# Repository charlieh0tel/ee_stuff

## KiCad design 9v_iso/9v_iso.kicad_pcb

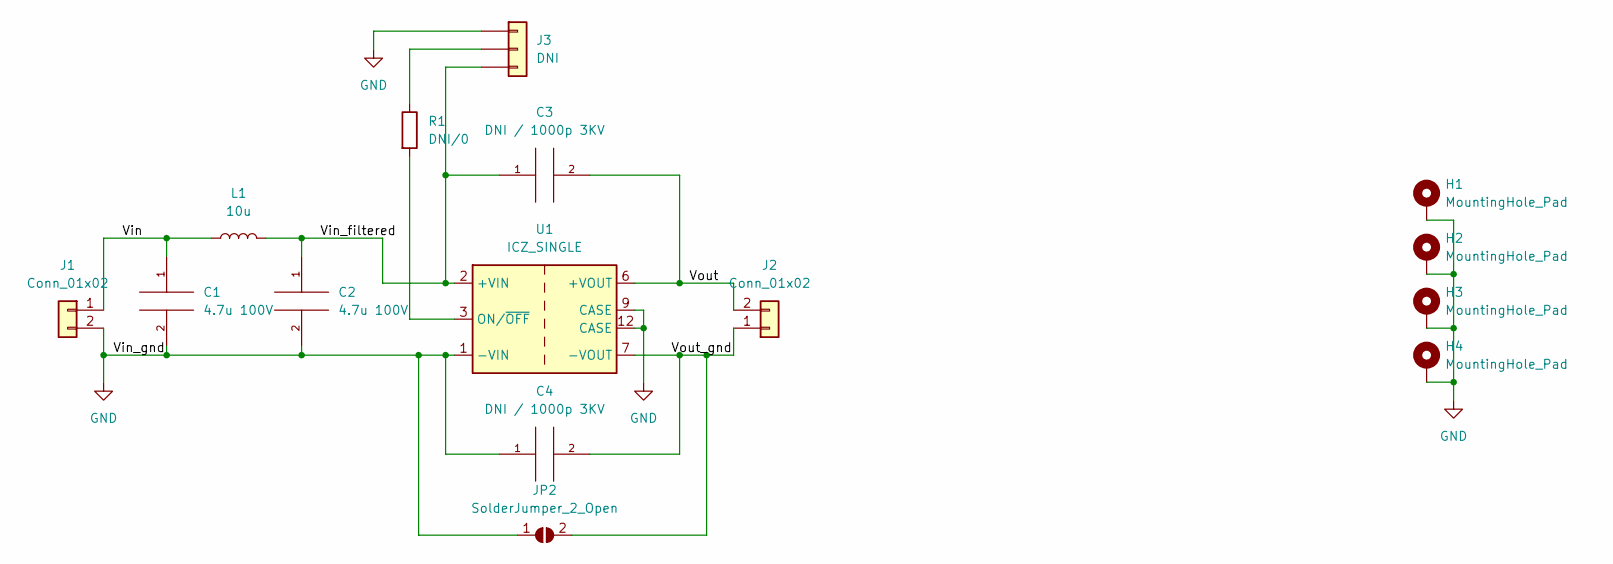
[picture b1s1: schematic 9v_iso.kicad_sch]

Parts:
C1, C2: 4.7u 100V; C_1210_3225Metric_Pad1.33x2.70mm_HandSolder
C3, C4: DNI / 1000p 3KV; C_1812_4532Metric_Pad1.57x3.40mm_HandSolder
H1, H2, H3, H4: MountingHole_Pad; MountingHole_3mm_Pad
J1, J2: Conn_01x02; TerminalBlock_bornier-2_P5.08mm
J3: DNI; PinHeader_1x03_P2.54mm_Vertical
JP2: SolderJumper_2_Open; SolderJumper-2_P1.3mm_Open_RoundedPad1.0x1.5mm
L1: 10u; L_Taiyo-Yuden_NR-24xx_HandSoldering
R1: DNI/0; R_0805_2012Metric_Pad1.20x1.40mm_HandSolder
U1: ICZ_SINGLE; CONV_ICZ0912S12

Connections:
/Vin: C1.1, J1.1, L1.1
/Vin_filtered: C2.1, C3.1, J3.3, L1.2, U1.2 (+VIN)
/Vout: C3.2, J2.2, U1.6 (+VOUT)
/Vout_gnd: C4.2, J2.1, JP2.2 (B), U1.7 (-VOUT)
GND: C1.2, C2.2, C4.1, H1.1, H2.1, H3.1, H4.1, J1.2, J3.1, JP2.1 (A), U1.1 (-VIN), U1.9 (CASE), U1.12 (CASE)
unnamed: J3.2, R1.1
unnamed: R1.2, U1.3 (ON/~OFF)

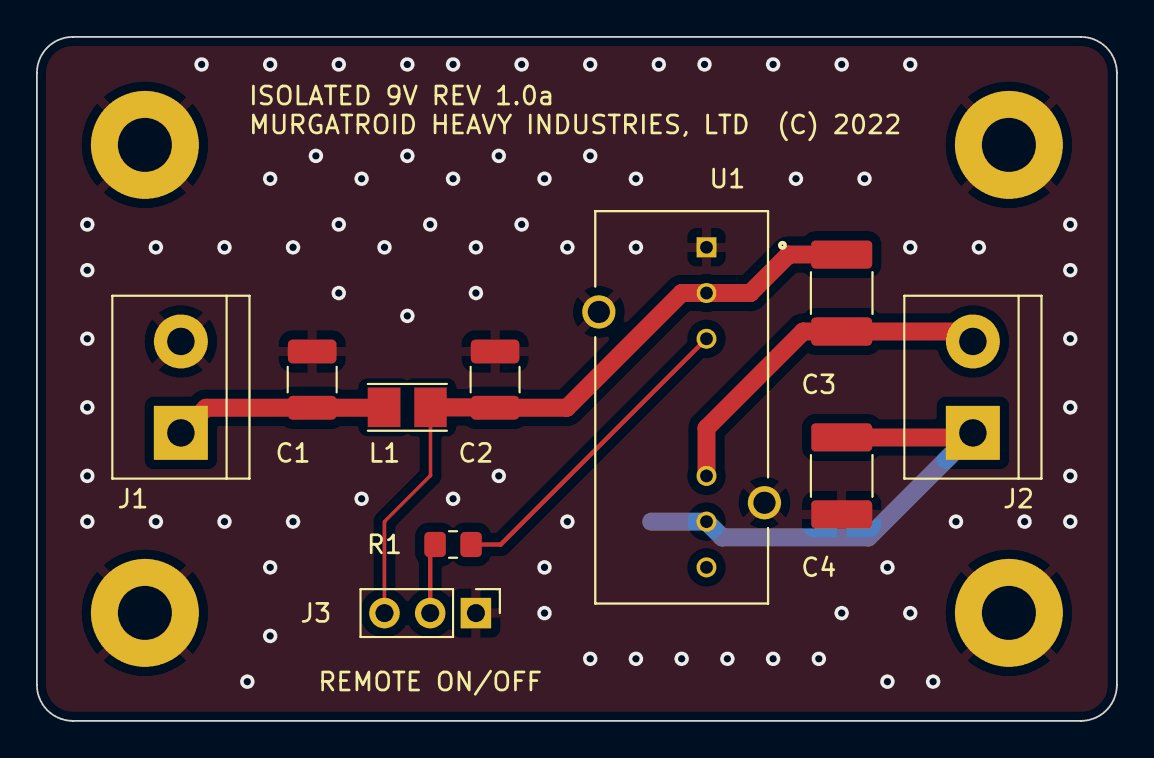
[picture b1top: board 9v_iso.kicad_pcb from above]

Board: 2 copper layers, 60.0 x 38.0 mm, 15 parts (1 on the bottom side), 7 nets.

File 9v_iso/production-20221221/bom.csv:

Designator,Footprint,Quantity,Value,LCSC Part #
"C1, C2",C_1210_3225Metric_Pad1.33x2.70mm_HandSolder,2,4.7u 100V,
"C3, C4",C_1812_4532Metric_Pad1.57x3.40mm_HandSolder,2,DNI / 1000p 3KV,
"H1, H2, H3, H4",MountingHole_3mm_Pad,4,MountingHole_Pad,
"J1, J2",TerminalBlock_bornier-2_P5.08mm,2,Conn_01x02,
J3,PinHeader_1x03_P2.54mm_Vertical,1,DNI,
JP2,SolderJumper-2_P1.3mm_Open_RoundedPad1.0x1.5mm,1,SolderJumper_2_Open,
L1,L_Taiyo-Yuden_NR-24xx_HandSoldering,1,10u,
R1,R_0805_2012Metric_Pad1.20x1.40mm_HandSolder,1,DNI/0,
U1,CONV_ICZ0912S12,1,ICZ_SINGLE,

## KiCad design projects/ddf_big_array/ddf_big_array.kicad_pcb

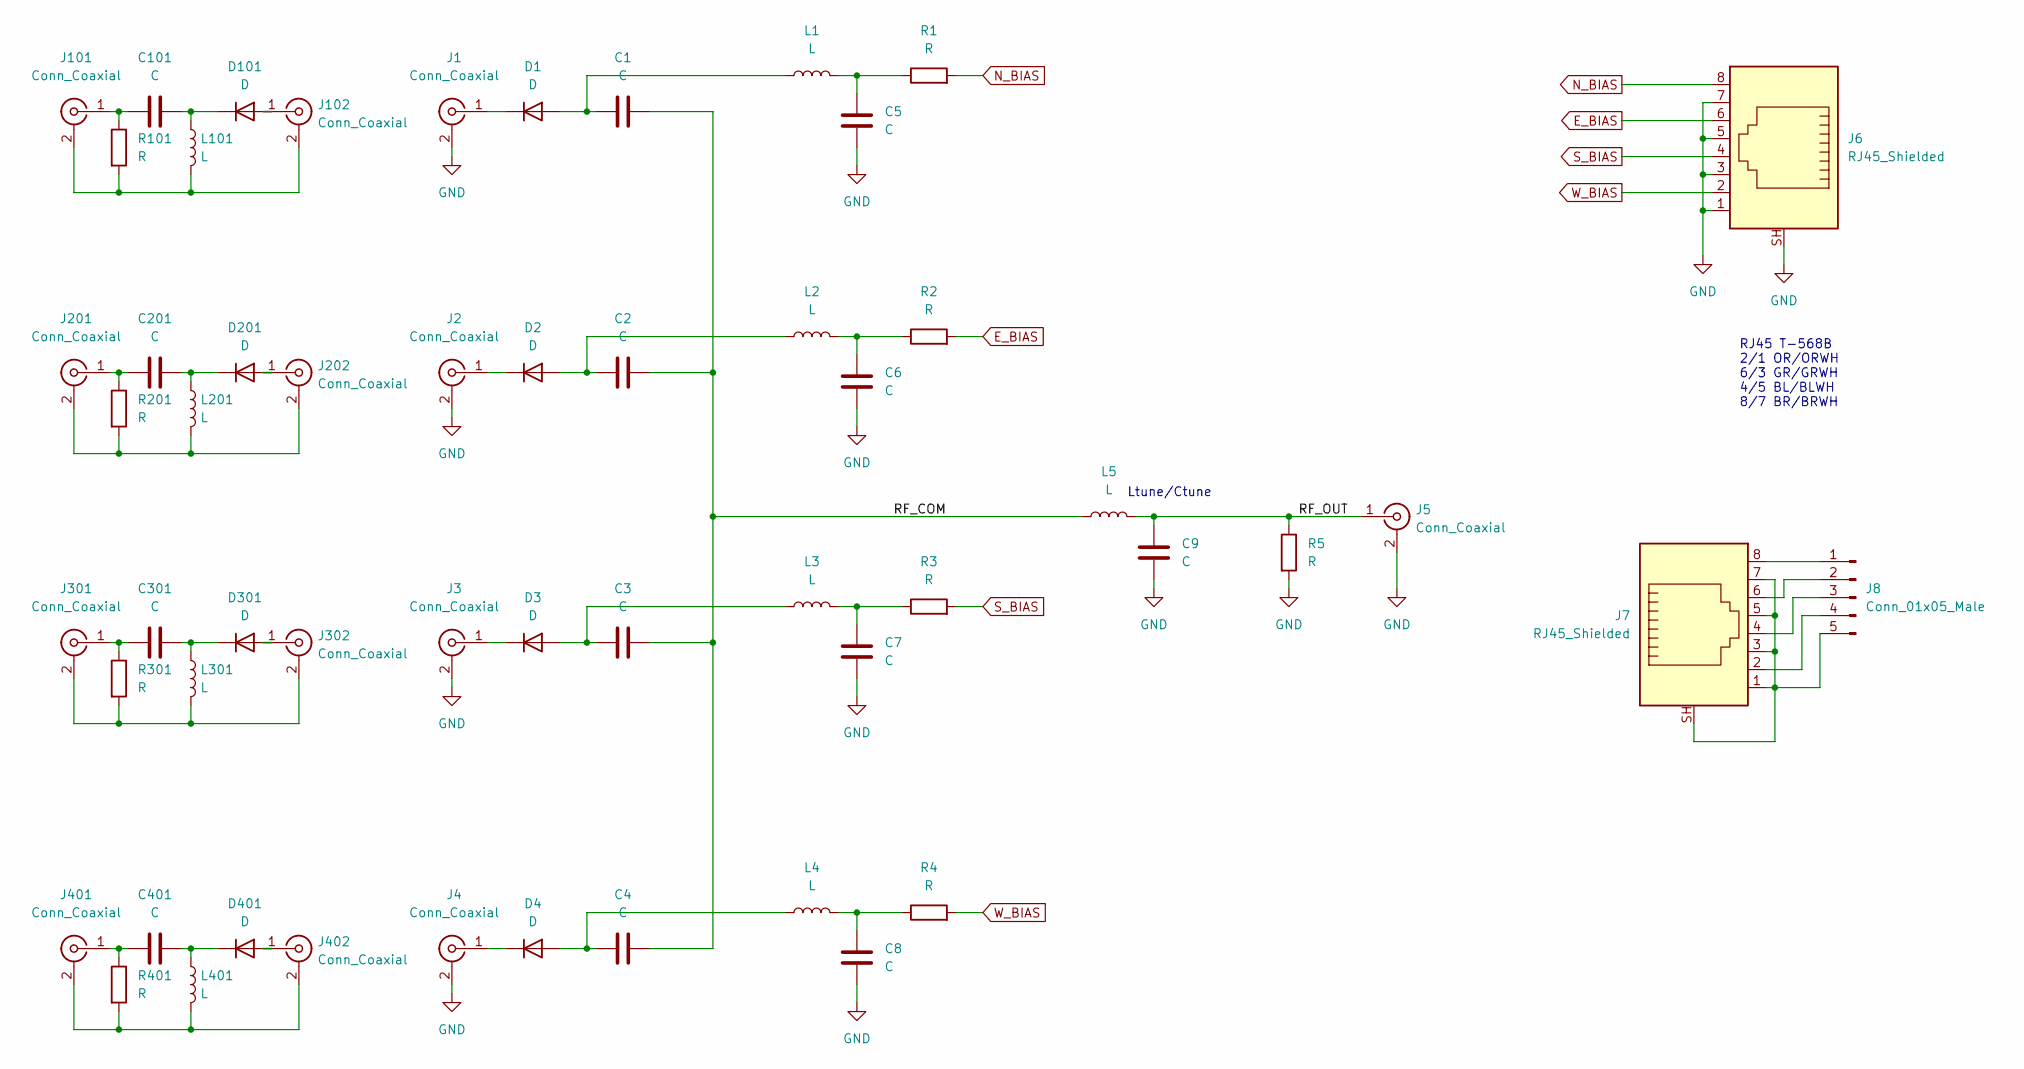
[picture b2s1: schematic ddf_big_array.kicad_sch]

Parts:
C1, C2, C3, C4, C5, C6, C7, C8, C9, C101, C201, C301, C401: C; C_0402_1005Metric_Pad0.74x0.62mm_HandSolder
D1, D2, D3, D4, D101, D201, D301, D401: D; D_SOD-523
J1, J2, J3, J4, J102, J202, J302, J402: Conn_Coaxial; SMA_Amphenol_132203-12_Horizontal
J5: Conn_Coaxial; SMA_Molex_73251-2200_Horizontal
J6, J7: RJ45_Shielded; RJ45_Wuerth_7499010001A_Horizontal
J8: Conn_01x05_Male; PinHeader_1x05_P2.54mm_Vertical
J101, J201, J301, J401: Conn_Coaxial; SMA_Amphenol_132134_Vertical
L1, L2, L3, L4, L5, L101, L201, L301, L401: L; L_0402_1005Metric_Pad0.77x0.64mm_HandSolder
R1, R2, R3, R4, R5, R101, R201, R301, R401: R; R_0402_1005Metric_Pad0.72x0.64mm_HandSolder

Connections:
/RF_COM: C1.2, C2.2, C3.2, C4.2, L5.1
/RF_OUT: C9.1, J5.1 (In), L5.2, R5.1
E_BIAS: J6.6, R2.2
GND: C5.2, C6.2, C7.2, C8.2, C9.2, J1.2 (Ext), J2.2 (Ext), J3.2 (Ext), J4.2 (Ext), J5.2 (Ext), J6.1, J6.3, J6.5, J6.7, J6.SH, R5.2
N_BIAS: J6.8, R1.2
unnamed: C1.1, D1.2 (A), L1.1
unnamed: C2.1, D2.2 (A), L2.1
unnamed: C3.1, D3.2 (A), L3.1
unnamed: C4.1, D4.2 (A), L4.1
unnamed: C5.1, L1.2, R1.1
unnamed: C6.1, L2.2, R2.1
unnamed: C7.1, L3.2, R3.1
unnamed: C8.1, L4.2, R4.1
unnamed: C101.1, J101.1 (In), R101.1
unnamed: C101.2, D101.1 (K), L101.1
unnamed: C201.1, J201.1 (In), R201.1
unnamed: C201.2, D201.1 (K), L201.1
unnamed: C301.1, J301.1 (In), R301.1
unnamed: C301.2, D301.1 (K), L301.1
unnamed: C401.1, J401.1 (In), R401.1
unnamed: C401.2, D401.1 (K), L401.1
unnamed: D1.1 (K), J1.1 (In)
unnamed: D2.1 (K), J2.1 (In)
unnamed: D3.1 (K), J3.1 (In)
unnamed: D4.1 (K), J4.1 (In)
unnamed: D101.2 (A), J102.1 (In)
unnamed: D201.2 (A), J202.1 (In)
unnamed: D301.2 (A), J302.1 (In)
unnamed: D401.2 (A), J402.1 (In)
unnamed: J7.1, J7.3, J7.5, J7.7, J7.SH, J8.5
unnamed: J7.2, J8.4
unnamed: J7.4, J8.3
unnamed: J7.6, J8.2
unnamed: J7.8, J8.1
unnamed: J101.2 (Ext), J102.2 (Ext), L101.2, R101.2
unnamed: J201.2 (Ext), J202.2 (Ext), L201.2, R201.2
unnamed: J301.2 (Ext), J302.2 (Ext), L301.2, R301.2
unnamed: J401.2 (Ext), J402.2 (Ext), L401.2, R401.2
S_BIAS: J6.4, R3.2
W_BIAS: J6.2, R4.2

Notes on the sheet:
RJ45 T-568B 2/1 OR/ORWH 6/3 GR/GRWH 4/5 BL/BLWH 8/7 BR/BRWH
Ltune/Ctune

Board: 2 copper layers, 55 parts (0 on the bottom side), 40 nets, no tracks yet.

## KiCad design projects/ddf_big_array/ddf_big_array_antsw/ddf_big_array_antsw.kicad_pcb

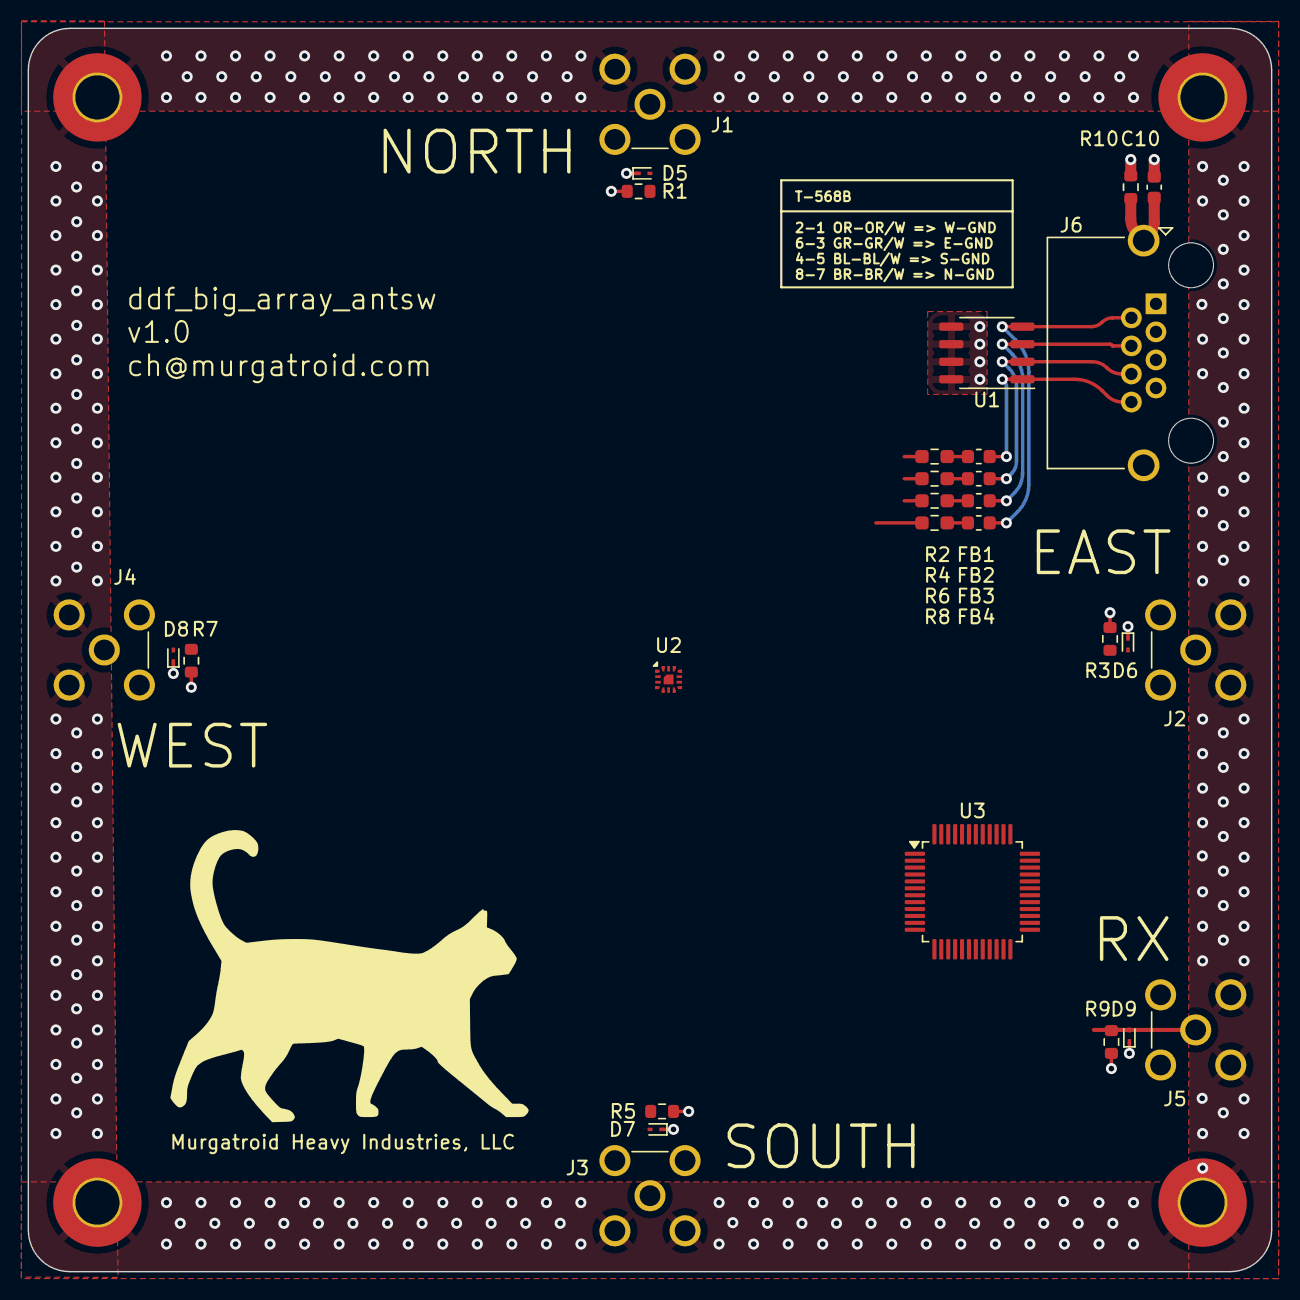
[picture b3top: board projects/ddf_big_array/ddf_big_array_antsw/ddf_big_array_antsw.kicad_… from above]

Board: 4 copper layers, 90.0 x 90.0 mm, 33 parts (0 on the bottom side), 16 nets.

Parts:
C10: 1n NP0 50V; C_0603_1608Metric
D5, D6, D7, D8, D9: ESD7951ST5G; D_SOD-923
FB1, FB2, FB3, FB4: 600R @ 100 MHz; L_0603_1608Metric
H1, H2, H3, H4: MountingHole; MountingHole_3.2mm_M3_Pad_TopBottom
J1, J2, J3, J4, J5: Conn_Coaxial; SMA_Horizontal
J6: RJ45_Shielded; RJ45_Amphenol_RJHSE5380
R1, R3, R5, R7, R9, R10: 100K; R_0603_1608Metric
R2, R4, R6, R8: 270; R_0603_1608Metric_Pad0.98x0.95mm_HandSolder
U1: SMDA05; SO-8_3.9x4.9mm_P1.27mm
U2: SKY13414-485LF; Skyworks_SKY13575_639LF
U3: STM32G0B1CBT; LQFP-48_7x7mm_P0.5mm

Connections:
+3V3: U3.4 (VBAT), U3.5 (VREF+), U3.6 (VDD/VDDA)
/E_IN: D6.2 (A2), J2.1 (In), R3.1
/N_IN: D5.2 (A2), J1.1 (In), R1.1
/RF_OUT: D9.2 (A2), J5.1 (In), R9.1
/RJ_SHIELD: C10.1, J6.SH, R10.1
/S_IN: D7.2 (A2), J3.1 (In), R5.1
/W_IN: D8.2 (A2), J4.1 (In), R7.1
E_BIAS: FB2.1, R4.2
GND: C10.2, D5.1 (A1), D6.1 (A1), D7.1 (A1), D8.1 (A1), D9.1 (A1), H1.1, H2.1, H3.1, H4.1, J1.2 (Ext), J2.2 (Ext), J3.2 (Ext), J4.2 (Ext), J5.2 (Ext), J6.1, J6.3, J6.5, J6.7, R1.2, R3.2, R5.2, R7.2, R9.2, R10.2, U1.5 (D2), U1.6 (C2), U1.7 (B2), U1.8 (A2), U2.15 (GND), U3.7 (VSS/VSSA)
N_BIAS: FB1.1, R2.2
unnamed: FB1.2, J6.8
unnamed: FB2.2, J6.6
unnamed: FB3.2, J6.4
unnamed: FB4.2, J6.2
S_BIAS: FB3.1, R6.2
W_BIAS: FB4.1, R8.2

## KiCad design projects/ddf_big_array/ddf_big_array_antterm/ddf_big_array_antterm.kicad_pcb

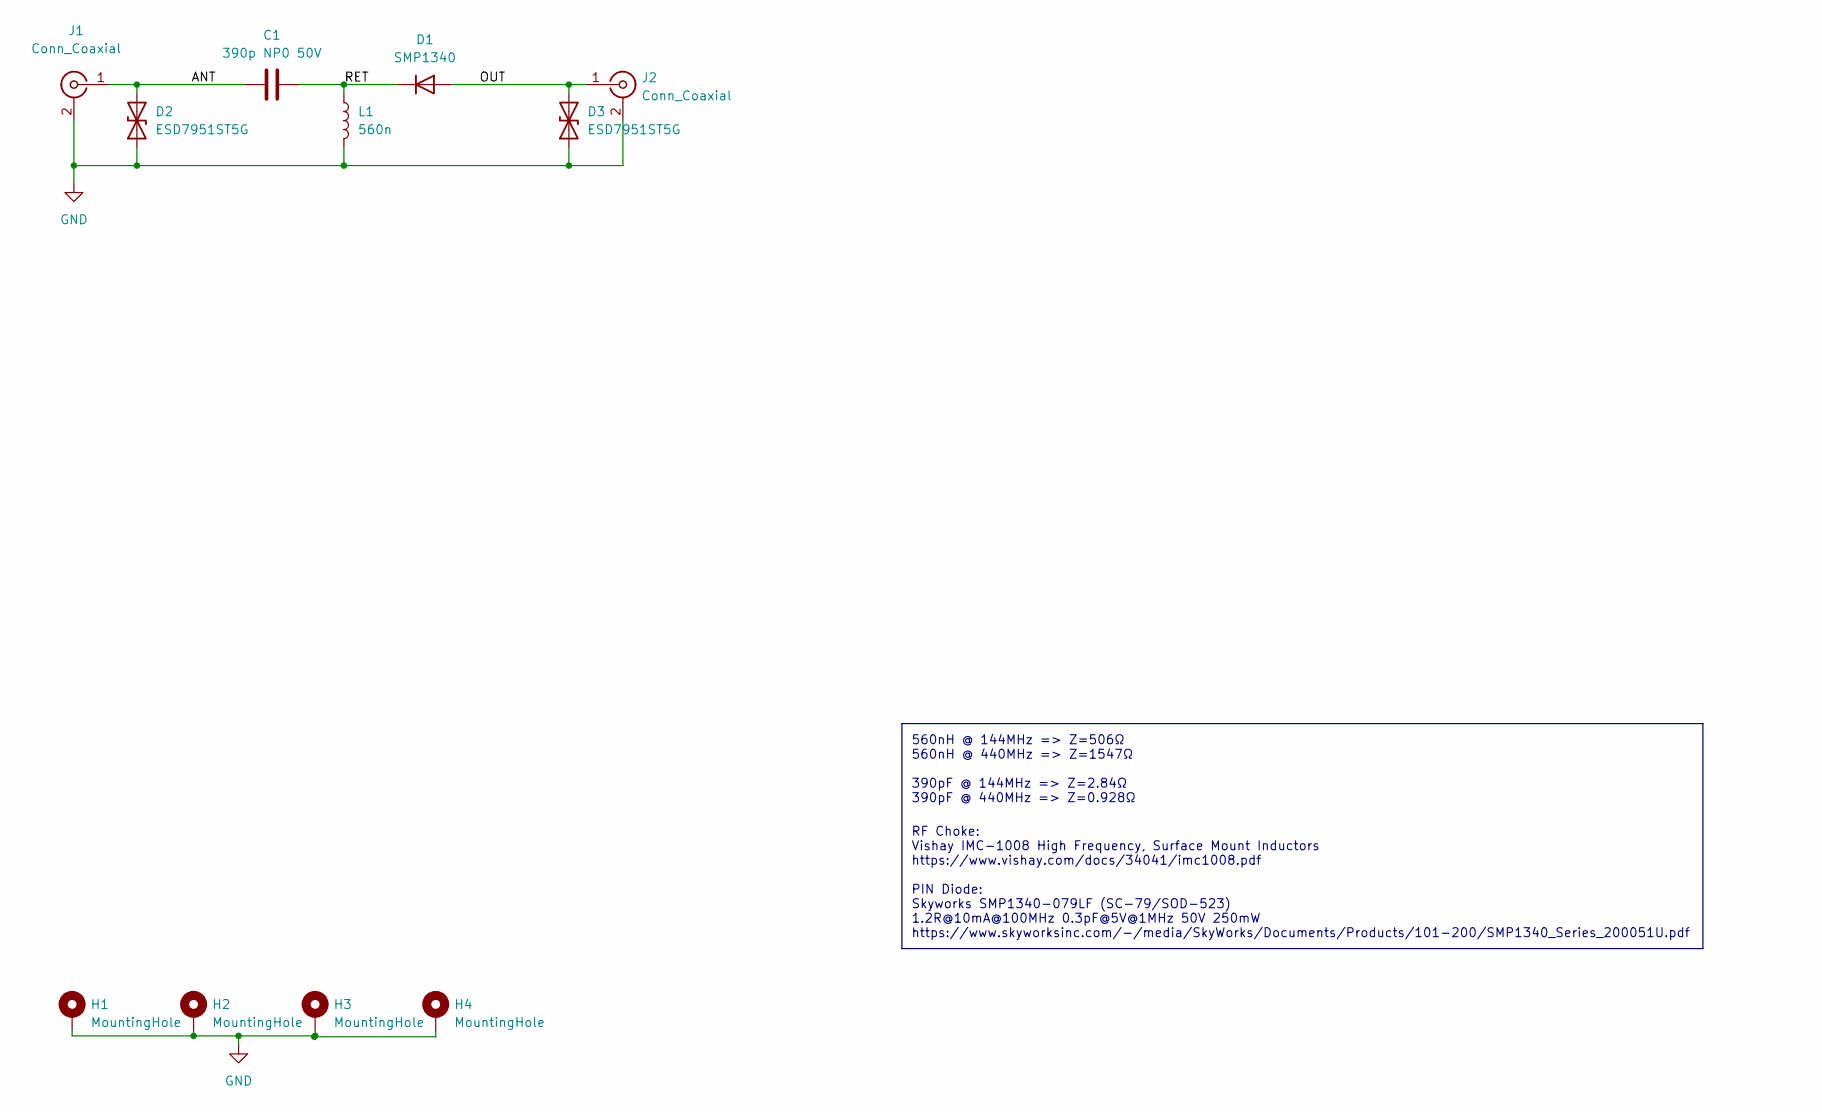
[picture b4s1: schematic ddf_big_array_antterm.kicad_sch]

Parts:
C1: 390p NP0 50V; C_0402_1005Metric; MPN GRM1555C1H391FA01D; LCSC C162100
D1: SMP1340; D_SOD-523; MPN SMP1340-079LF; LCSC C5365278
D2, D3: ESD7951ST5G; D_SOD-923; MPN ESD7951ST5G; LCSC C94375
H1, H2, H3, H4: MountingHole; MountingHole_3.2mm_M3_Pad_TopBottom
J1: Conn_Coaxial; SMA_Molex-73391-0070_Vertical; LCSC C2874833
J2: Conn_Coaxial; SMA_Horizontal; LCSC C1509208
L1: 560n; IMC1008; MPN IMC1008ERR56J; LCSC C5365279

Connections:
/ANT: C1.1, D2.2 (A2), J1.1 (In)
/OUT: D1.2 (A), D3.2 (A2), J2.1 (In)
/RET: C1.2, D1.1 (K), L1.1
GND: D2.1 (A1), D3.1 (A1), H1.1, H2.1, H3.1, H4.1, J1.2 (Ext), J2.2 (Ext), L1.2

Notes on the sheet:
RF Choke: Vishay IMC-1008 High Frequency, Surface Mount Inductors https://www.vishay.com/docs/34041/imc1008.pdf PIN Diode: Skyworks SMP1340-079LF (SC-79/SOD-523) 1.2R@10mA@100MHz 0.3pF@5V@1MHz 50V 250mW https://www.skyworksinc.com/-/media/SkyWorks/Documents/Products/101-200/SMP1340_Series_200051U.p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
560nH @ 144MHz => Z=506Ω 560nH @ 440MHz => Z=1547Ω 390pF @ 144MHz => Z=2.84Ω 390pF @ 440MHz => Z=0.928Ω

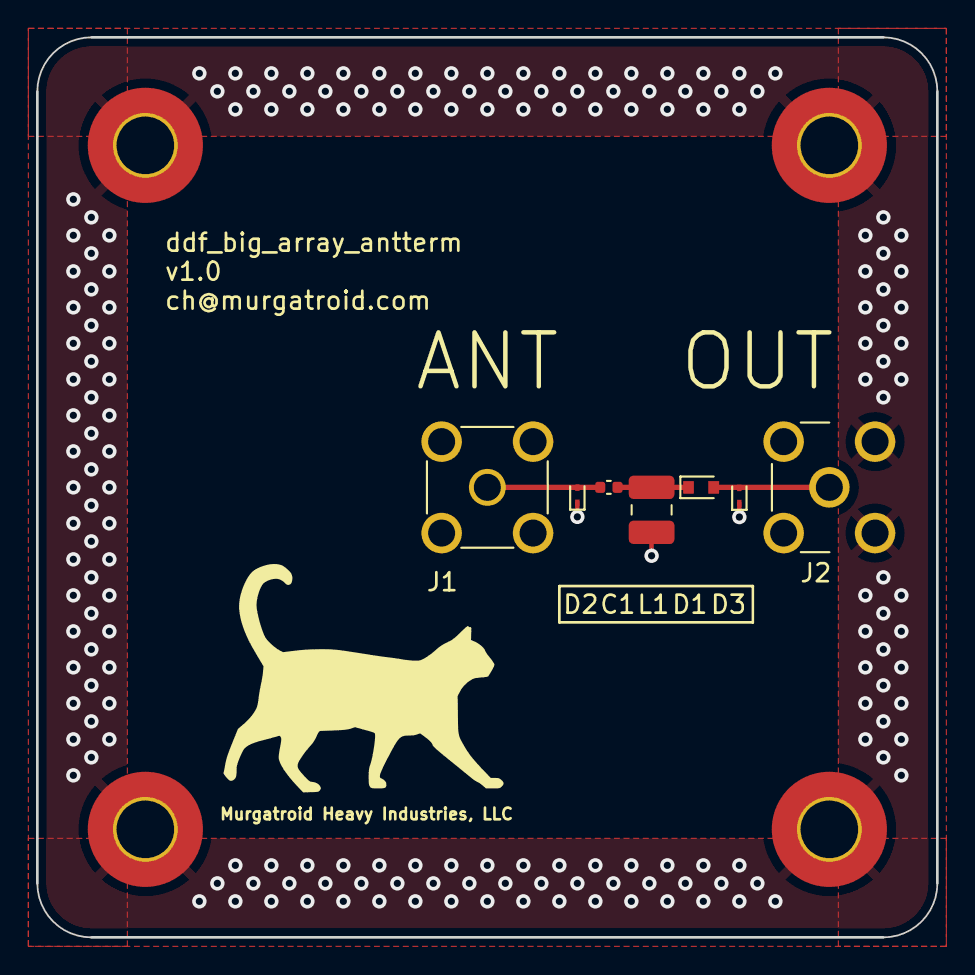
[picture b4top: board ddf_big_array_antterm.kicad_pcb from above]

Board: 4 copper layers, 50.0 x 50.0 mm, 11 parts (0 on the bottom side), 4 nets.

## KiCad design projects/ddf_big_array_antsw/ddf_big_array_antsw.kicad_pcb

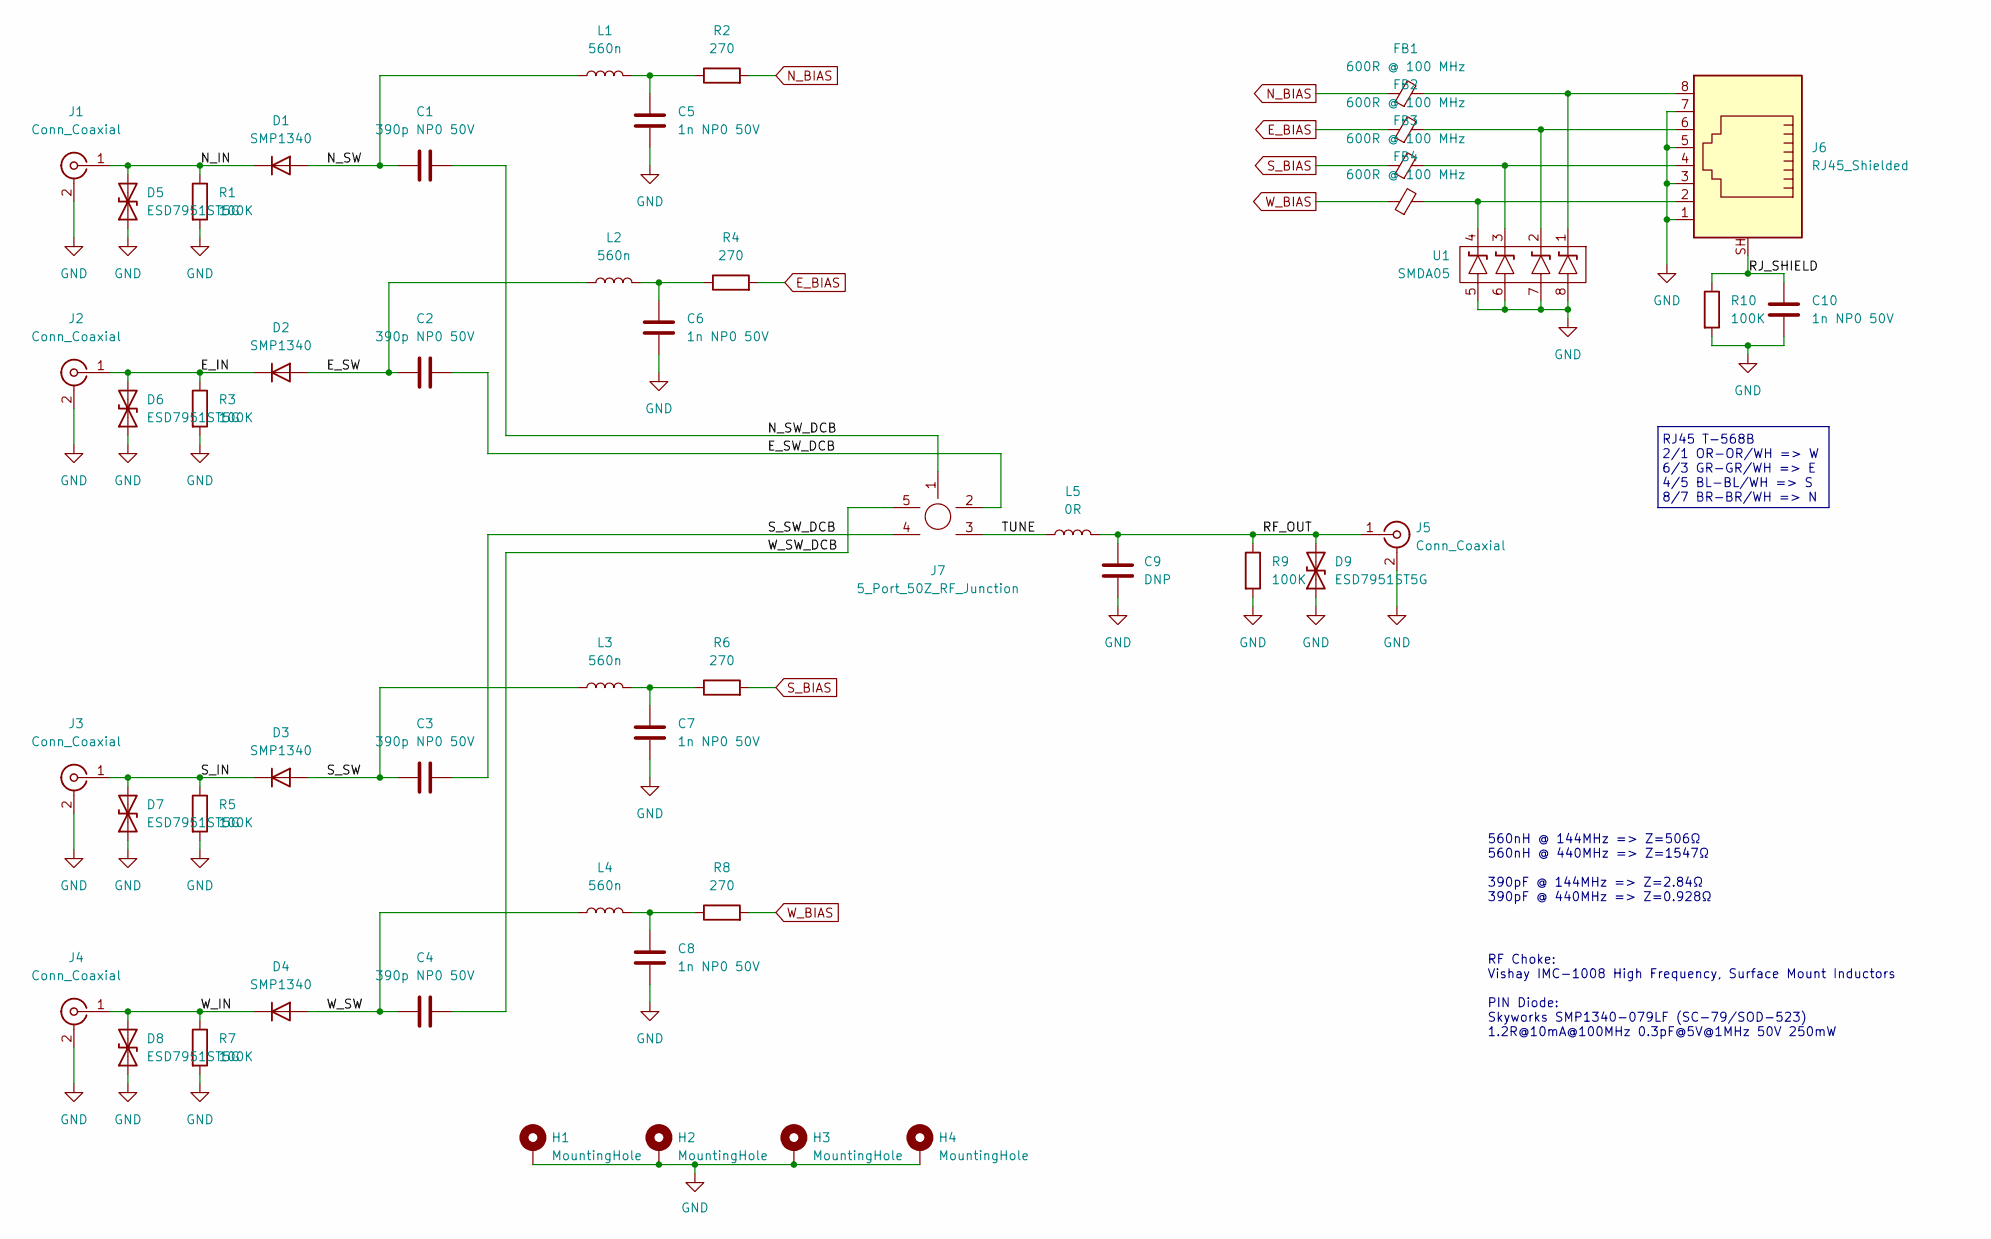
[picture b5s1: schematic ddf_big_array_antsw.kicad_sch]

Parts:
C1, C2, C3, C4: 390p NP0 50V; C_0603_1608Metric; MPN GRM1555C1H391FA01D; LCSC C162100
C5, C6, C7, C8, C10: 1n NP0 50V; C_0603_1608Metric; MPN GRM1885C1H102JA01D; LCSC C77026
C9: DNP; C_0603_1608Metric; LCSC DNP
D1, D2, D3, D4: SMP1340; D_SOD-523; MPN SMP1340-079LF; LCSC C5365278
D5, D6, D7, D8, D9: ESD7951ST5G; D_SOD-923; MPN ESD7951ST5G; LCSC C94375
FB1, FB2, FB3, FB4: 600R @ 100 MHz; L_0603_1608Metric; MPN GZ1608D601TF; LCSC C94375
H1, H2, H3, H4: MountingHole; MountingHole_3.2mm_M3_Pad_TopBottom
J1, J2, J3, J4, J5: Conn_Coaxial; SMA_Horizontal; LCSC C1509208
J6: RJ45_Shielded; RJ45_Amphenol_RJHSE5380; LCSC C464586
J7: 5_Port_50Z_RF_Junction; 5 Port 50Z RF Junction
L1, L2, L3, L4: 560n; IMC1008; MPN IMC1008ERR56J; LCSC C5365279
L5: 0R; L_0402_1005Metric_Pad0.77x0.64mm_HandSolder; MPN 0402WGF0000TCE; LCSC C5365279
R1, R3, R5, R7, R9, R10: 100K; R_0603_1608Metric; MPN RC0603FR-07100KL; LCSC C14675
R2, R4, R6, R8: 270; R_0603_1608Metric_Pad0.98x0.95mm_HandSolder; MPN RC0603FR-07270RL; LCSC C137754
U1: SMDA05; SO-8_3.9x4.9mm_P1.27mm; MPN SMDA05; LCSC C1978067

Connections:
/E_IN: D2.1 (K), D6.2 (A2), J2.1 (In), R3.1
/E_SW: C2.1, D2.2 (A), L2.1
/E_SW_DCB: C2.2, J7.2
/N_IN: D1.1 (K), D5.2 (A2), J1.1 (In), R1.1
/N_SW: C1.1, D1.2 (A), L1.1
/N_SW_DCB: C1.2, J7.1
/RF_OUT: C9.1, D9.2 (A2), J5.1 (In), L5.2, R9.1
/RJ_SHIELD: C10.1, J6.SH, R10.1
/S_IN: D3.1 (K), D7.2 (A2), J3.1 (In), R5.1
/S_SW: C3.1, D3.2 (A), L3.1
/S_SW_DCB: C3.2, J7.4
/TUNE: J7.3, L5.1
/W_IN: D4.1 (K), D8.2 (A2), J4.1 (In), R7.1
/W_SW: C4.1, D4.2 (A), L4.1
/W_SW_DCB: C4.2, J7.5
E_BIAS: FB2.1, R4.2
GND: C5.2, C6.2, C7.2, C8.2, C9.2, C10.2, D5.1 (A1), D6.1 (A1), D7.1 (A1), D8.1 (A1), D9.1 (A1), H1.1, H2.1, H3.1, H4.1, J1.2 (Ext), J2.2 (Ext), J3.2 (Ext), J4.2 (Ext), J5.2 (Ext), J6.1, J6.3, J6.5, J6.7, R1.2, R3.2, R5.2, R7.2, R9.2, R10.2, U1.5 (D2), U1.6 (C2), U1.7 (B2), U1.8 (A2)
N_BIAS: FB1.1, R2.2
unnamed: C5.1, L1.2, R2.1
unnamed: C6.1, L2.2, R4.1
unnamed: C7.1, L3.2, R6.1
unnamed: C8.1, L4.2, R8.1
unnamed: FB1.2, J6.8, U1.1 (A1)
unnamed: FB2.2, J6.6, U1.2 (B1)
unnamed: FB3.2, J6.4, U1.3 (C1)
unnamed: FB4.2, J6.2, U1.4 (D1)
S_BIAS: FB3.1, R6.2
W_BIAS: FB4.1, R8.2

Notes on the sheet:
RF Choke: Vishay IMC-1008 High Frequency, Surface Mount Inductors PIN Diode: Skyworks SMP1340-079LF (SC-79/SOD-523) 1.2R@10mA@100MHz 0.3pF@5V@1MHz 50V 250mW
560nH @ 144MHz => Z=506Ω 560nH @ 440MHz => Z=1547Ω 390pF @ 144MHz => Z=2.84Ω 390pF @ 440MHz => Z=0.928Ω
RJ45 T-568B 2/1 OR-OR/WH => W 6/3 GR-GR/WH => E 4/5 BL-BL/WH => S 8/7 BR-BR/WH => N

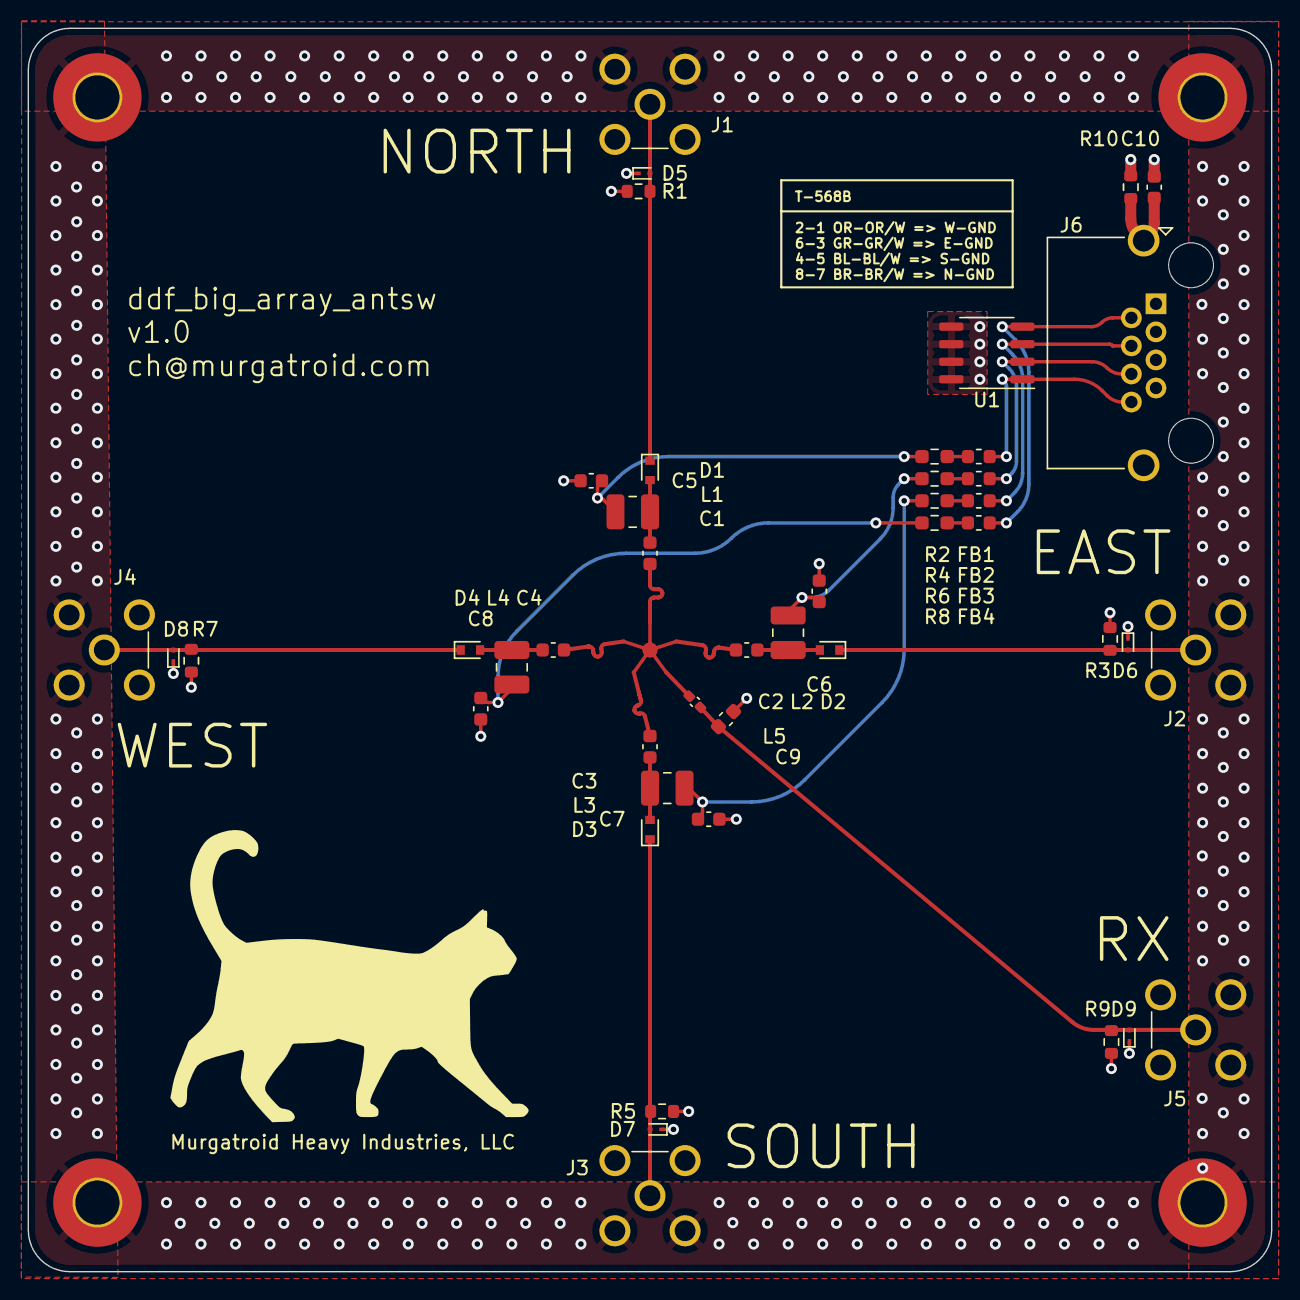
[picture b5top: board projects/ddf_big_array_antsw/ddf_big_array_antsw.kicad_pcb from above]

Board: 4 copper layers, 90.0 x 90.0 mm, 50 parts (0 on the bottom side), 28 nets.

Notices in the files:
9v_iso/9v_iso.kicad_pcb:
MURGATROID HEAVY INDUSTRIES, LTD  (C) 2022
